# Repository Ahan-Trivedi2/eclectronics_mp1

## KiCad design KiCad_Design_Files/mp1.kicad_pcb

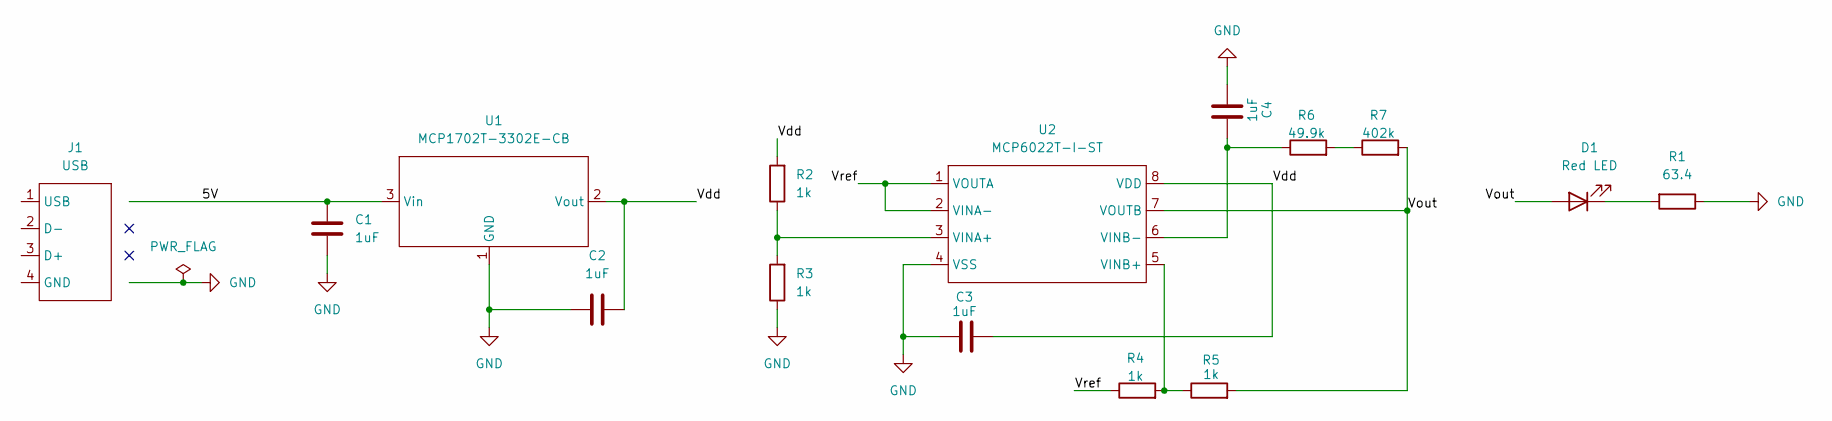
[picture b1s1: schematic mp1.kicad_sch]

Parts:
C1, C2, C3, C4: 1uF; C_0603_1608Metric
D1: Red LED; LED_0805_2012Metric
J1: USB; CONN_480370001_MOL
R1: 63.4; R_0603_1608Metric
R2, R3, R4, R5: 1k; R_0603_1608Metric
R6: 49.9k; R_0603_1608Metric
R7: 402k; R_0603_1608Metric
U1: MCP1702T-3302E-CB; SOT-23A_MC_MCH
U2: MCP6022T-I-ST; TSSOP8_MC_MCH

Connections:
/5V: C1.1, J1.1 (USB), U1.3 (Vin)
/Vdd: C2.1, C3.1, R2.2, U1.2 (Vout), U2.8 (VDD)
/Vout: D1.2 (A), R5.2, R7.2, U2.7 (VOUTB)
/Vref: R4.1, U2.1 (VOUTA), U2.2 (VINA-)
GND: C1.2, C2.2, C3.2, C4.2, J1.4 (GND), R1.1, R3.1, U1.1 (GND), U2.4 (VSS)
unnamed: D1.1 (K), R1.2
unnamed: R6.2, R7.1
unnamed: R2.1, R3.2, U2.3 (VINA+)
unnamed: R4.2, R5.1, U2.5 (VINB+)
unnamed: C4.1, R6.1, U2.6 (VINB-)

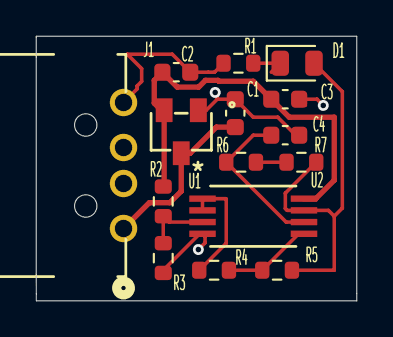
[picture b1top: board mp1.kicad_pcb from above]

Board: 2 copper layers, 17.8 x 14.7 mm, 15 parts (0 on the bottom side), 10 nets.

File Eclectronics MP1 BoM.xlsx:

Reference | Qty | Value | Part Description | Digikey Catalog # | Manufacturer Part #
J1 | 1.0 | USB_A | CONN PLUG USB 4POS RT ANG PCB | WM17117-ND | 4.80370001E8
U1 | 1.0 | MCP1702T-3302E/CB | IC REG LIN 3.3V 250MA SOT23A-3 | MCP1702T-3302E/CBCT-ND | MCP1702T-3302E/CB
U2 | 1.0 | MCP6022 | IC OPAMP GP 10MHZ RRO 8TSSOP | MCP6022T-I/STCT-ND | MCP6022T-I/ST
D1 | 1.0 | LTST-C171KRKT | LED RED CLEAR 0805 SMD | 160-1427-1-ND | LTST-C171KRKT
C1, C2, C3, C4 | 4.0 | 1uF | CAP CER 1UF 25V X7R 0603 | 399-7376-1-ND | C0603C105K3RACTU
R2, R3, R4, R5 | 4.0 | 1kΩ | RES SMD 1K OHM 1% 1/10W 0603 | 311-1.00KHRCT-ND | RC0603FR-071KL
R7 | 1.0 | 402kΩ | RES SMD 402K OHM 1% 1/10W 0603 | 311-402KHRCT-ND | RC0603FR-07402KL
R6 | 1.0 | 49.9kΩ | RES SMD 49.9K OHM 1% 1/10W 0603 | 311-49.9KHRCT-ND | RC0603FR-0749K9L
R1 | 1.0 | 63.4Ω | RES SMD 63.4 OHM 1% 1/10W 0603 | 311-63.4HRCT-ND | RC0603FR-0763R4L
